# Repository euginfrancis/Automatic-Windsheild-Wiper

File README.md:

# Automatic-Windsheild-Wiper
Atmega8 based automatic windsheild wiper
More details visit: http://circuits-4u.blogspot.in/

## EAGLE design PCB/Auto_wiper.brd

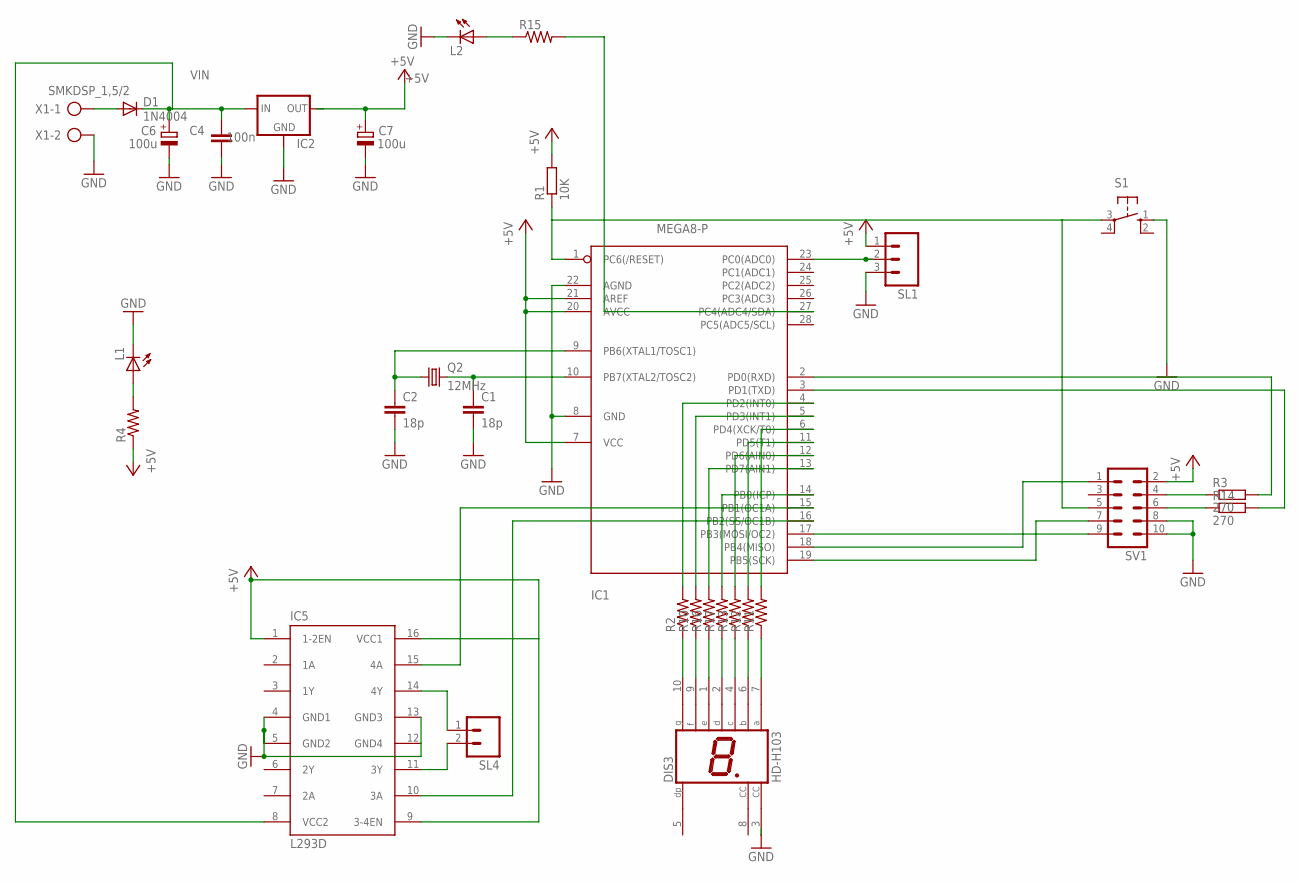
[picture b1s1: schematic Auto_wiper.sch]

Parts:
C1, C2: 18p; C025-024X044
C4: 100n; C025-030X050
C6, C7: 100u; E3,5-8
D1: 1N4004; DO41-10
DIS3: HD-H103; HDSP-M
IC1: MEGA8-P; DIL28-3
IC2: 78XXS
IC5: L293D; DIL16
L1, L2: LED5MM
Q2: 12MHz; HC49/S
R1: 10K; 0207/10
R2, R4, R10, R11, R12, R13, R15, R16, R17: R-US_0207/10; 0207/10
R3, R14: 270; 0207/10
S1: 10-XX; B3F-10XX
SL1: M03; 03P
SL4: M02; 02P
SV1: ML10
X1: SMKDSP_1,5/2

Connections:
+5V: C7.+, IC1.7 (VCC), IC1.20 (AVCC), IC1.21 (AREF), IC2.OUT, IC5.1 (1-2EN), IC5.9 (3-4EN), IC5.16 (VCC1), R1.2, R4.1, SL1.1, SV1.2
GND: C1.2, C2.2, C4.1, C6.-, C7.-, DIS3.3 (CC), IC1.8 (GND), IC1.22 (AGND), IC2.GND, IC5.4 (GND1), IC5.5 (GND2), IC5.12 (GND4), IC5.13 (GND3), L1.K (C), L2.K (C), S1.1 (S), SL1.3, SV1.8, SV1.10, X1.2
MOTOR1: IC1.15 (PB1(OC1A)), IC5.15 (4A)
MOTOR9: IC1.17 (PB3(MOSI/OC2)), SV1.9
unnamed: L1.A, R4.2
unnamed: IC1.19 (PB5(SCK)), SV1.7
unnamed: C1.1, IC1.10 (PB7(XTAL2/TOSC2)), Q2.2
unnamed: C2.1, IC1.9 (PB6(XTAL1/TOSC1)), Q2.1
unnamed: DIS3.10 (G), R2.1
unnamed: R3.1, SV1.4
unnamed: IC1.2 (PD0(RXD)), R3.2
unnamed: IC1.3 (PD1(TXD)), R14.2
unnamed: DIS3.9 (F), R10.1
unnamed: IC1.27 (PC4(ADC4/SDA)), R15.2
unnamed: IC1.18 (PB4(MISO)), SV1.1
unnamed: DIS3.6 (B), R12.1
unnamed: IC1.1 (PC6(/RESET)), R1.1, S1.3, SV1.5
unnamed: DIS3.1 (E), R16.1
unnamed: DIS3.4 (C), R13.1
unnamed: DIS3.2 (D), R17.1
unnamed: DIS3.7 (A), R11.1
unnamed: IC1.11 (PD5(T1)), R12.2
unnamed: IC1.6 (PD4(XCK/T0)), R11.2
unnamed: IC1.5 (PD3(INT1)), R10.2
unnamed: IC1.4 (PD2(INT0)), R2.2
unnamed: IC1.23 (PC0(ADC0)), SL1.2
unnamed: IC1.16 (PB2(SS/OC1B)), IC5.10 (3A)
unnamed: R14.1, SV1.6
unnamed: L2.A, R15.1
unnamed: IC1.14 (PB0(ICP)), R17.2
unnamed: IC1.12 (PD6(AIN0)), R13.2
unnamed: IC1.13 (PD7(AIN1)), R16.2
unnamed: IC5.14 (4Y), SL4.1
unnamed: IC5.11 (3Y), SL4.2
PWRIN: D1.A, X1.1
VIN: C4.2, C6.+, D1.C, IC2.IN, IC5.8 (VCC2)

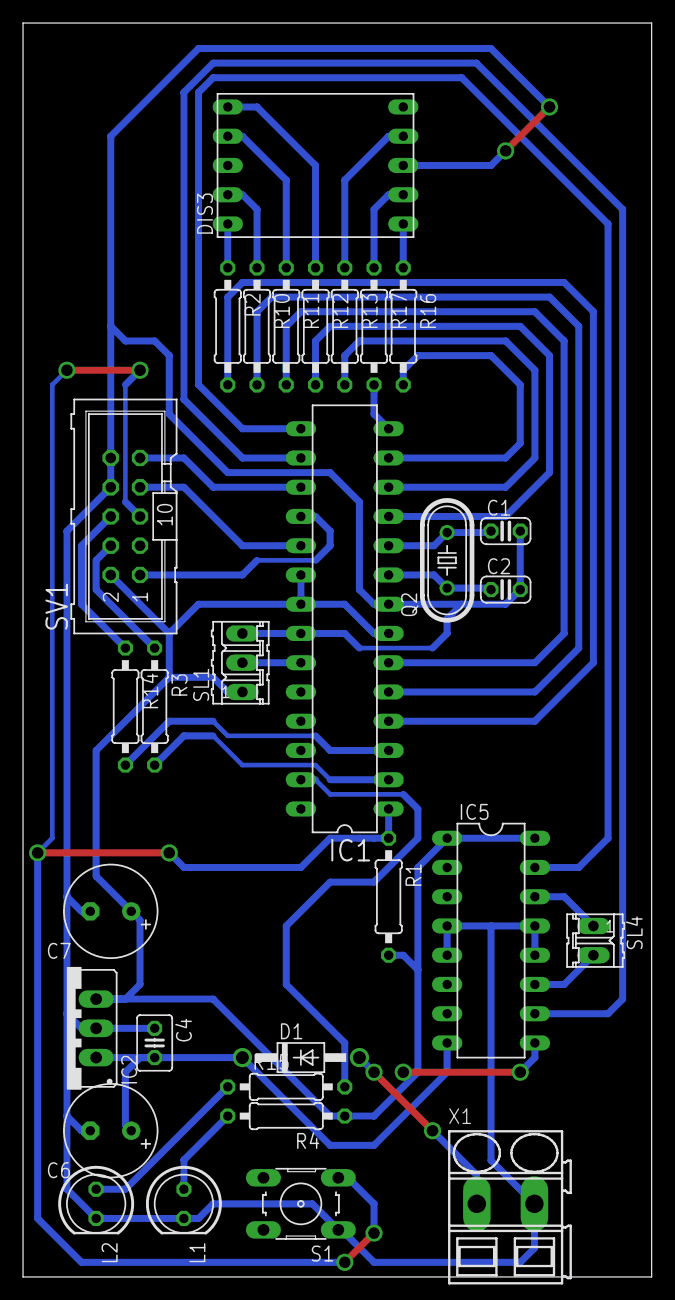
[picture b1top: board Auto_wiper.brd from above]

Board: 2 copper layers, 54.6 x 108.9 mm, 30 parts (0 on the bottom side), 36 nets.

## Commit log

2015-08-09 :confetti_ball: Added .gitattributes & .gitignore files
2015-08-09 init files
